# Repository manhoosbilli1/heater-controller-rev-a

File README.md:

# HEATER CONTROLLER REV_A

Battery-powered heater controller, 10 A switching, hierarchical schematic (ATtiny + OLED + dual-battery taps)

## At a Glance

- **Status**: Routed
- **Board size**: 47.24 x 45.82 mm
- **Layers**: 2
- **Components**: 75
- **Key ICs**:
  - U1: ATtiny3216-S
  - U2: DS18B20U
  - U3: TP4056
  - U4: INA234AxYBJ
  - U5,U6: TPS73001SF6
  - U7: TPS22997RYZR

## Schematic

Full PDF: [reports/schematic.pdf](reports/schematic.pdf)

## Component Roles

- **ATtiny** (in hierarchical sub-sheets) - main MCU; reads temperature and PWM-drives the heater MOSFET
- **CSD17578Q3A** (Q2) - 30 V, 100 A, 1.8 m-Ohm N-channel MOSFET; switches the heater load directly (low Rds(on) keeps conduction losses small at 10 A)
- **WS2812B** (D5) - status RGB LED
- **USB-C** charging input (power-only, 6P)
- **Dual battery taps** (TP1-TP4: BAT1+, BAT1-, BAT2+, BAT2-) for parallel/series battery configurations
- **Heater output taps** (TP5/TP6: HEATER_T1, HEATER_T2)
- Hierarchical schematic split across: Block Diagram, Project Architecture, Power-Sequencing, and Section A/B sub-sheets

## PCB

**Top copper**

**Bottom copper**

## Bill of Materials

| Refs | Value | Footprint | Qty | MPN | LCSC |
|------|-------|-----------|----:|-----|------|
| C1,C3-C7,C10,C12 | 100n | PCM_JLCPCB:C_0402 | 8 |  |  |
| C2 | 100u | Capacitor_SMD:C_0805_2012Metric | 1 |  | [C141660](https://www.lcsc.com/product-detail/_C141660.html) |
| C8,C9,C11,C13 | 2.2u | Capacitor_SMD:C_0805_2012Metric | 4 |  |  |
| D1,D6,D7 | Red | PCM_JLCPCB:D_0603 | 3 |  | [C2286](https://www.lcsc.com/product-detail/_C2286.html) |
| D2 | White | PCM_JLCPCB:D_0603 | 1 |  | [C2290](https://www.lcsc.com/product-detail/_C2290.html) |
| D3 | Yellow | PCM_JLCPCB:D_0603 | 1 |  | [C89811](https://www.lcsc.com/product-detail/_C89811.html) |
| D4 | Green | PCM_JLCPCB:D_0603 | 1 |  | [C122984](https://www.lcsc.com/product-detail/_C122984.html) |
| D5 | WS2812B | PCM_JLCPCB:LED_WS2812B_PLCC4_5.0x5.0mm_P3.2mm | 1 |  | [C22461793](https://www.lcsc.com/product-detail/_C22461793.html) |
| J5 | USB_C_Receptacle_PowerOnly_6P | Connector_USB:USB_C_Receptacle_GCT_USB4135-GF-A_6P_TopMnt_Horizontal | 1 |  |  |
| Q2 | CSD17578Q3A | mosfet_ti:PDFN3333-8_L3.1-W3.2-P0.65-LS3.4-BL | 1 |  |  |
| R1 | 4.7k | Resistor_SMD:R_0402_1005Metric | 1 |  |  |
| R2 | 1.2k | Resistor_SMD:R_0402_1005Metric | 1 |  |  |
| R3,R4 | 5.1k | Resistor_SMD:R_0402_1005Metric | 2 |  |  |
| R5,R6,R11,R12,R14,R15,R18,R19,R21,R24,R25 | 10k | Resistor_SMD:R_0402_1005Metric | 11 |  |  |
| R7-R10 | 330 | PCM_JLCPCB:R_0402 | 4 |  |  |
| R13 | 8m | Resistor_SMD:R_2512_6332Metric | 1 |  | [C2904240](https://www.lcsc.com/product-detail/_C2904240.html) |
| R16,R17 | 1k | PCM_JLCPCB:R_0402 | 2 |  |  |
| R20,R26 | 46k | Resistor_SMD:R_0402_1005Metric | 2 |  | [C3016791](https://www.lcsc.com/product-detail/_C3016791.html) |
| R23 | 330 | Resistor_SMD:R_0402_1005Metric | 1 |  |  |
| S1,S3 | Tactile Button, 160gf | PCM_JLCPCB:SW-SMD_4P-L5.1-W5.1-P3.70-LS6.5-TL-2 | 2 |  | [C318884](https://www.lcsc.com/product-detail/_C318884.html) |
| TP1 | BAT2+ | TestPoint:TestPoint_Pad_D4.0mm | 1 |  |  |
| TP2 | BAT2- | TestPoint:TestPoint_Pad_D4.0mm | 1 |  |  |
| TP3 | BAT1+ | TestPoint:TestPoint_Pad_D4.0mm | 1 |  |  |
| TP4 | BAT1- | TestPoint:TestPoint_Pad_D4.0mm | 1 |  |  |
| TP5 | HEATER_T2 | TestPoint:TestPoint_Pad_D4.0mm | 1 |  |  |
| TP6 | HEATER_T1 | TestPoint:TestPoint_Pad_D4.0mm | 1 |  |  |
| TP7,TP9,TP10 | IN+ | TestPoint:TestPoint_THTPad_2.0x2.0mm_Drill1.0mm | 3 |  |  |
| TP8 | IN- | TestPoint:TestPoint_THTPad_2.0x2.0mm_Drill1.0mm | 1 |  |  |
| TP11 | CT | TestPoint:TestPoint_THTPad_2.0x2.0mm_Drill1.0mm | 1 |  |  |
| TP12 | GATE | TestPoint:TestPoint_THTPad_2.0x2.0mm_Drill1.0mm | 1 |  |  |
| U1 | ATtiny3216-S | Package_SO:SOIC-20W_7.5x12.8mm_P1.27mm | 1 |  |  |
| U2 | DS18B20U | Package_SO:MSOP-8_3x3mm_P0.65mm | 1 |  |  |
| U3 | TP4056 | PCM_JLCPCB:ESOP-8_L4.9-W3.9-P1.27-LS6.0-BL-EP | 1 |  | [C16581](https://www.lcsc.com/product-detail/_C16581.html) |
| U4 | INA234AxYBJ | Package_BGA:Texas_DSBGA-8_0.705x1.468mm_Layout2x4_P0.4mm | 1 |  |  |
| U5,U6 | TPS73001SF6 | tps73001sf6:SOT-23-6_L2.9-W1.6-P0.95-LS2.8-BL | 2 |  |  |
| U7 | TPS22997RYZR | load_switch:UQFN-10_L2.0-W1.5-P0.50-TL | 1 |  |  |

_26 of 36 line items don't have an LCSC code in the schematic - search [LCSC](https://www.lcsc.com/) or [JLC parts search](https://jlcsearch.tscircuit.com/) by MPN or footprint when sourcing._

## Files

- `HEATER CONTROLLER REV_A.kicad_pro` - KiCad project
- `HEATER CONTROLLER REV_A.kicad_sch` - schematic source
- `HEATER CONTROLLER REV_A.kicad_pcb` - PCB layout source
- `reports/schematic.pdf` - full schematic (printable)
- `reports/bom.csv` - bill of materials
- `reports/pcb-top.svg`, `reports/pcb-bottom.svg` - copper artwork
- `reports/board-stats.json` - KiCad-generated board statistics

---

_Renders and metadata auto-generated by `Backup-KiCadProject.ps1` using KiCad 10.0._

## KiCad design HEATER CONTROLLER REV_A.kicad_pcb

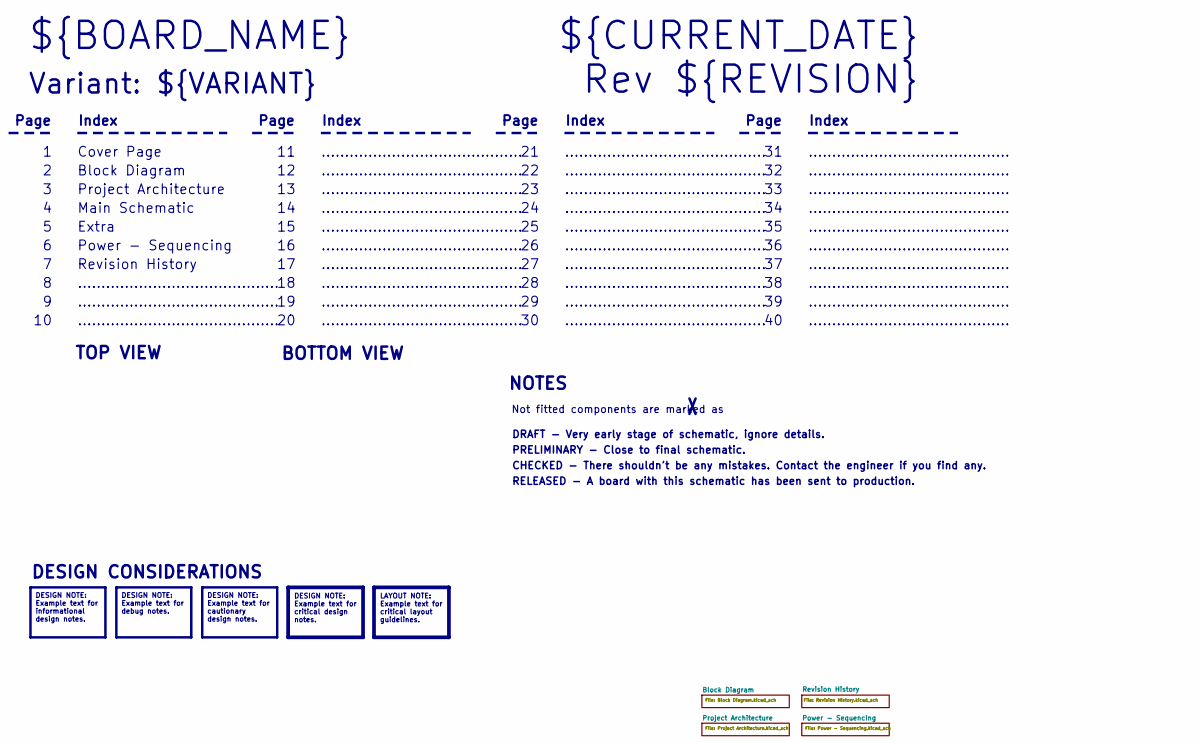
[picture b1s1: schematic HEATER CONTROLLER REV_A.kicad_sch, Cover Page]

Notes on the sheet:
BOTTOM VIEW
...........................................
RELEASED - A board with this schematic has been sent to production.
Page
TOP VIEW
Not fitted components are marked as
Index
PRELIMINARY - Close to final schematic.
Main Schematic
${CURRENT_DATE}
Variant: ${VARIANT}
Rev ${REVISION}
Extra
${BOARD_NAME}
DRAFT - Very early stage of schematic, ignore details.
Power - Sequencing
Block Diagram
Cover Page
NOTES
Project Architecture
CHECKED - There shouldn't be any mistakes. Contact the engineer if you find any.
DESIGN CONSIDERATIONS
Revision History
DESIGN NOTE: Example text for informational design notes.
LAYOUT NOTE: Example text for critical layout guidelines.
DESIGN NOTE: Example text for cautionary design notes.
DESIGN NOTE: Example text for debug notes.
DESIGN NOTE: Example text for critical design notes.

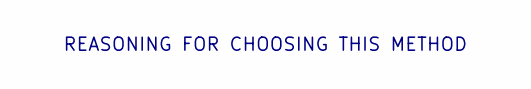
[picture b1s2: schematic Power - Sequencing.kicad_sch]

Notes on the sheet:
REASONING FOR CHOOSING THIS METHOD

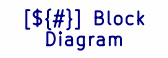
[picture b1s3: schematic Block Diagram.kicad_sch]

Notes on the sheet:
[${#}] ${TITLE}

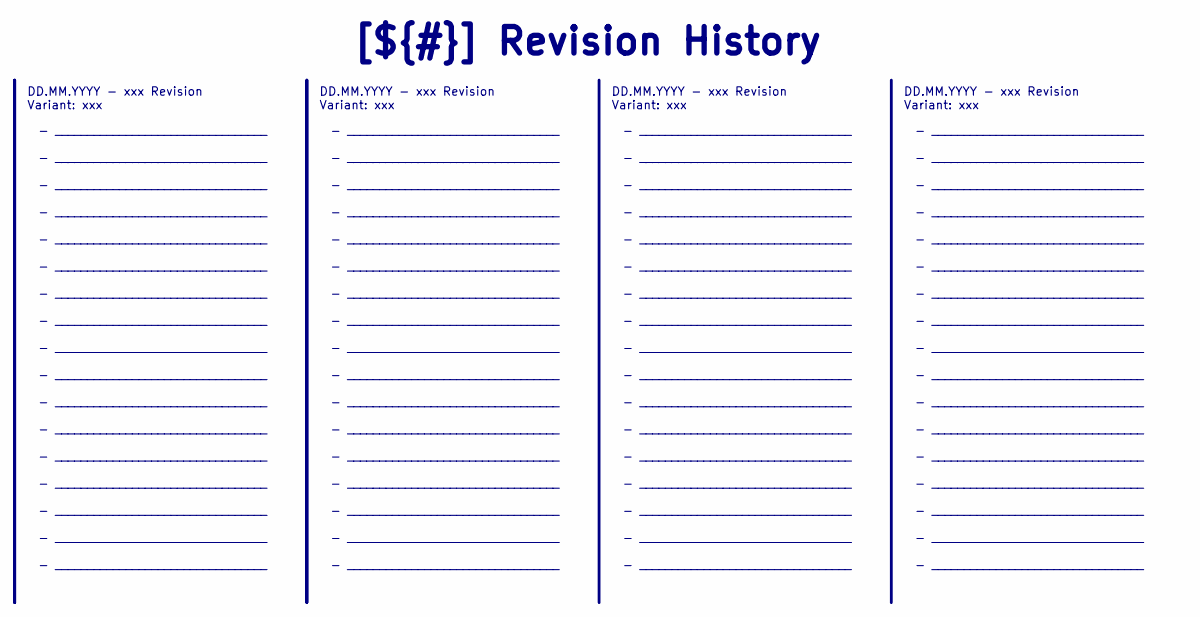
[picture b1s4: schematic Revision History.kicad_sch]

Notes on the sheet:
- _________________________________ - _________________________________ - _________________________________ - _________________________________ - _________________________________ - _________________________________ - _________________________________ - _________________________________ - _________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
DD.MM.YYYY - xxx Revision Variant: xxx
[${#}] ${TITLE}

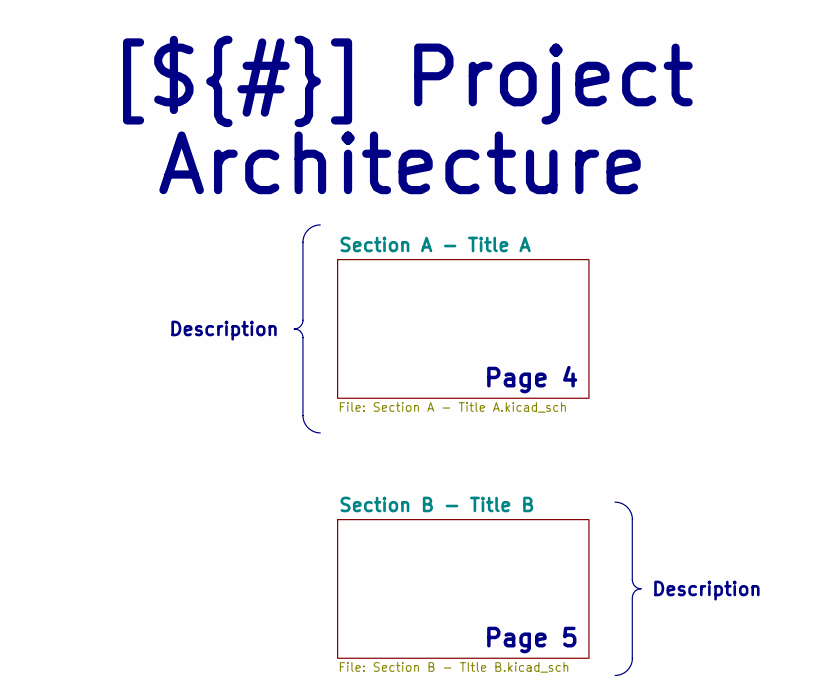
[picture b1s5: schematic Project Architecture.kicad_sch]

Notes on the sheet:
Page 4
Page 5
Description
[${#}] ${TITLE}

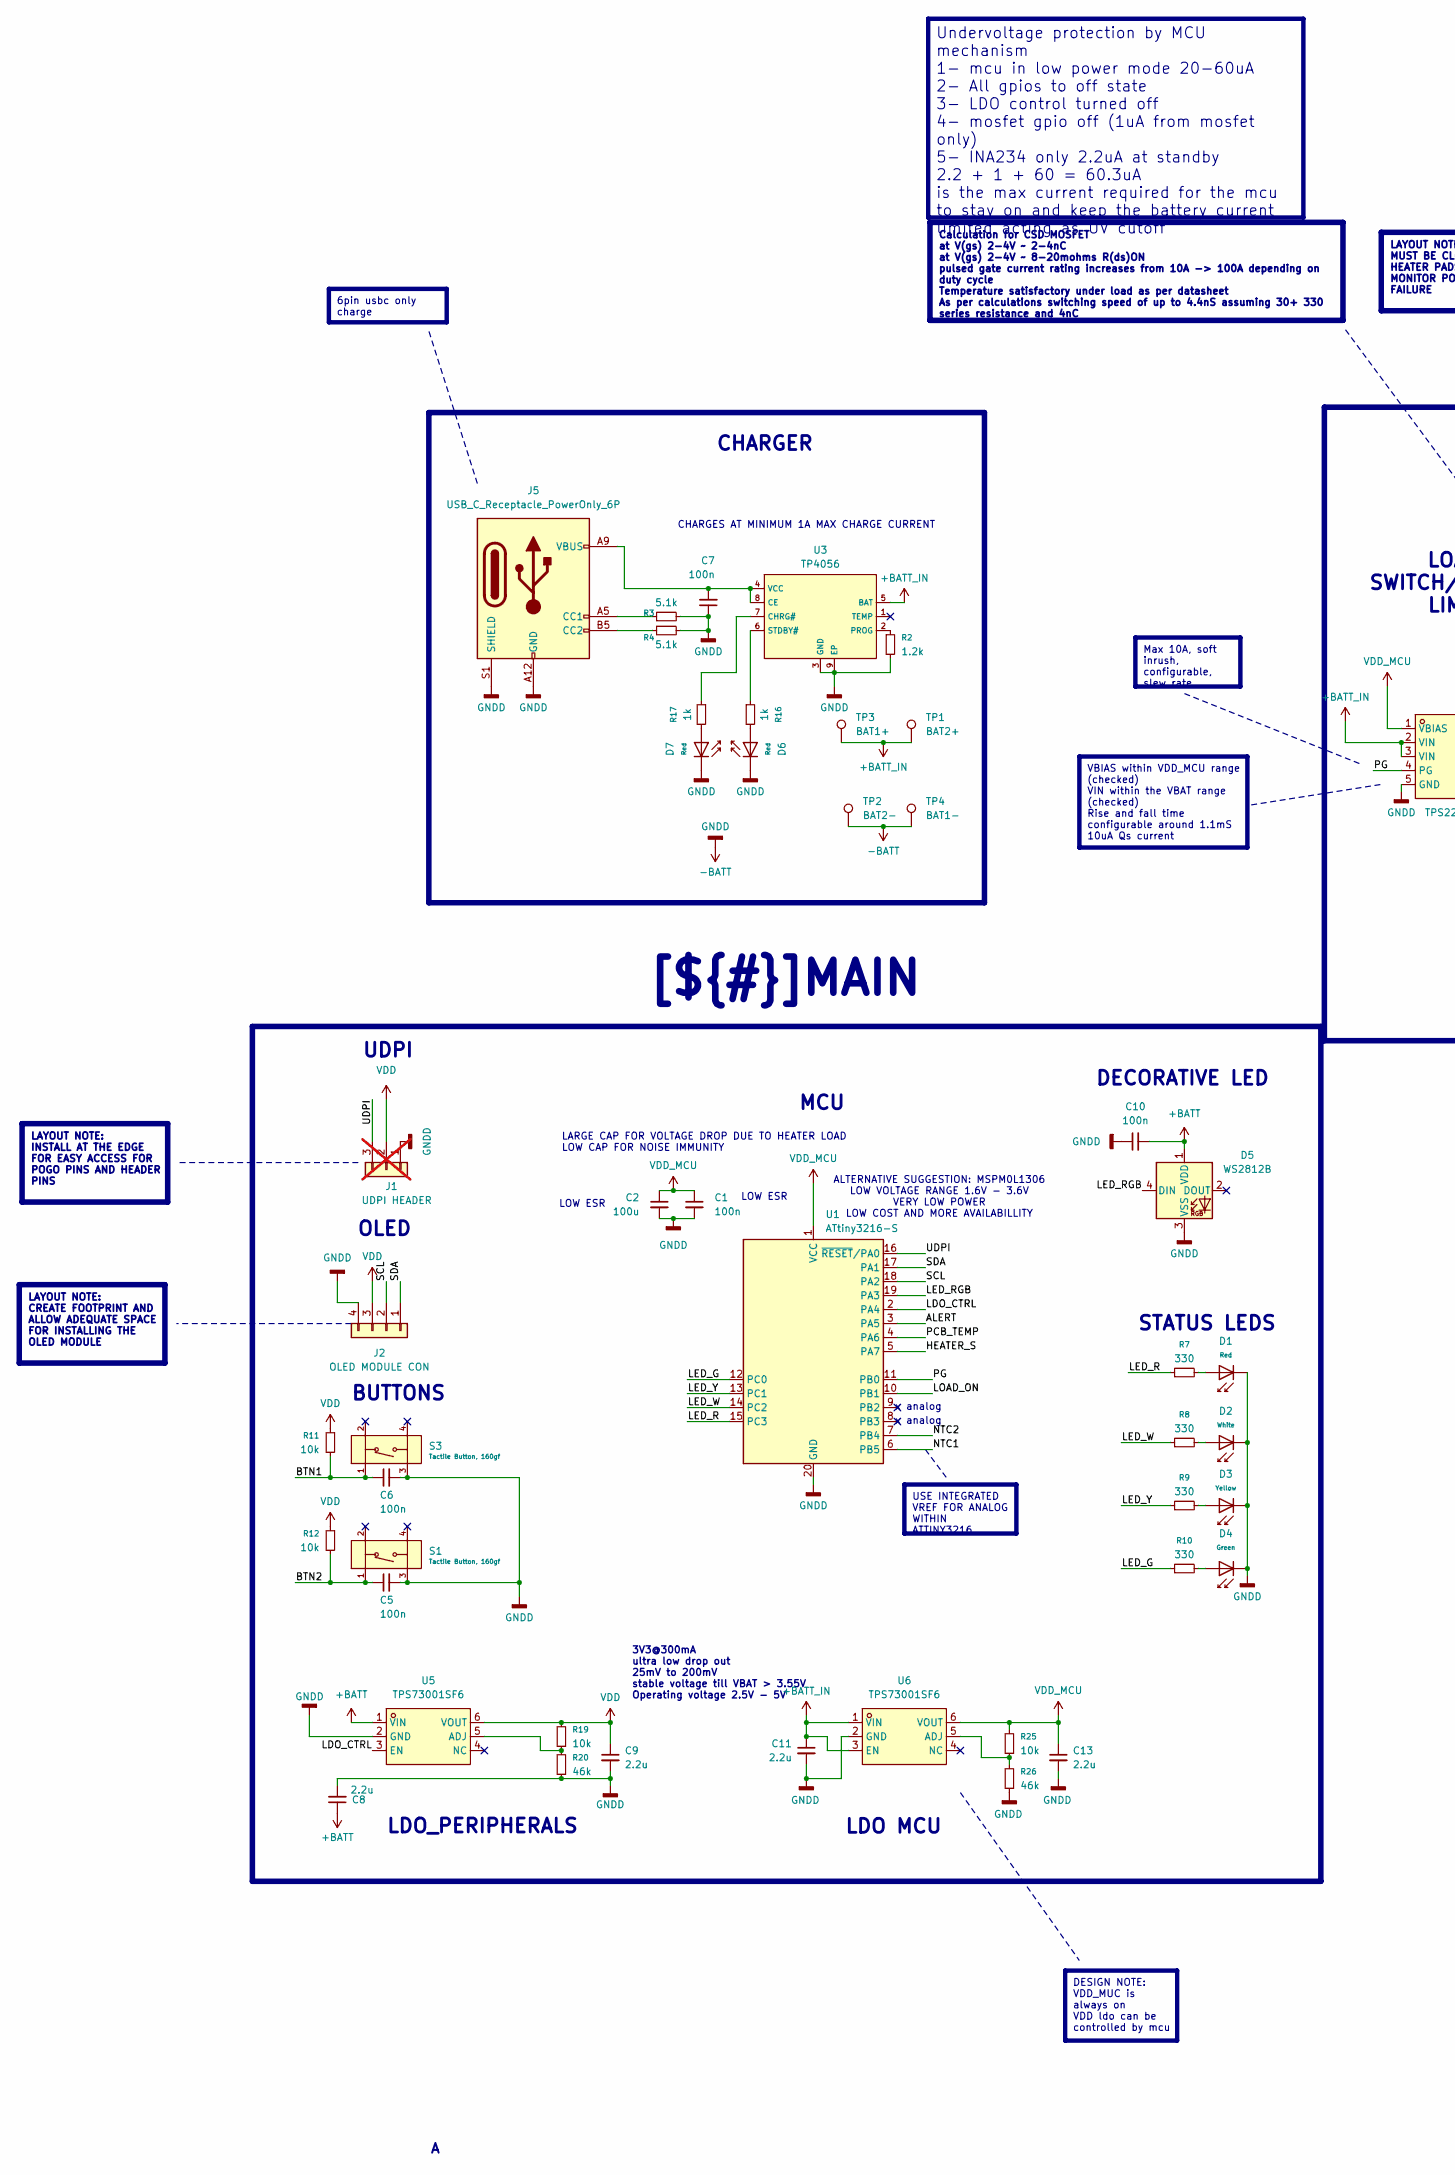
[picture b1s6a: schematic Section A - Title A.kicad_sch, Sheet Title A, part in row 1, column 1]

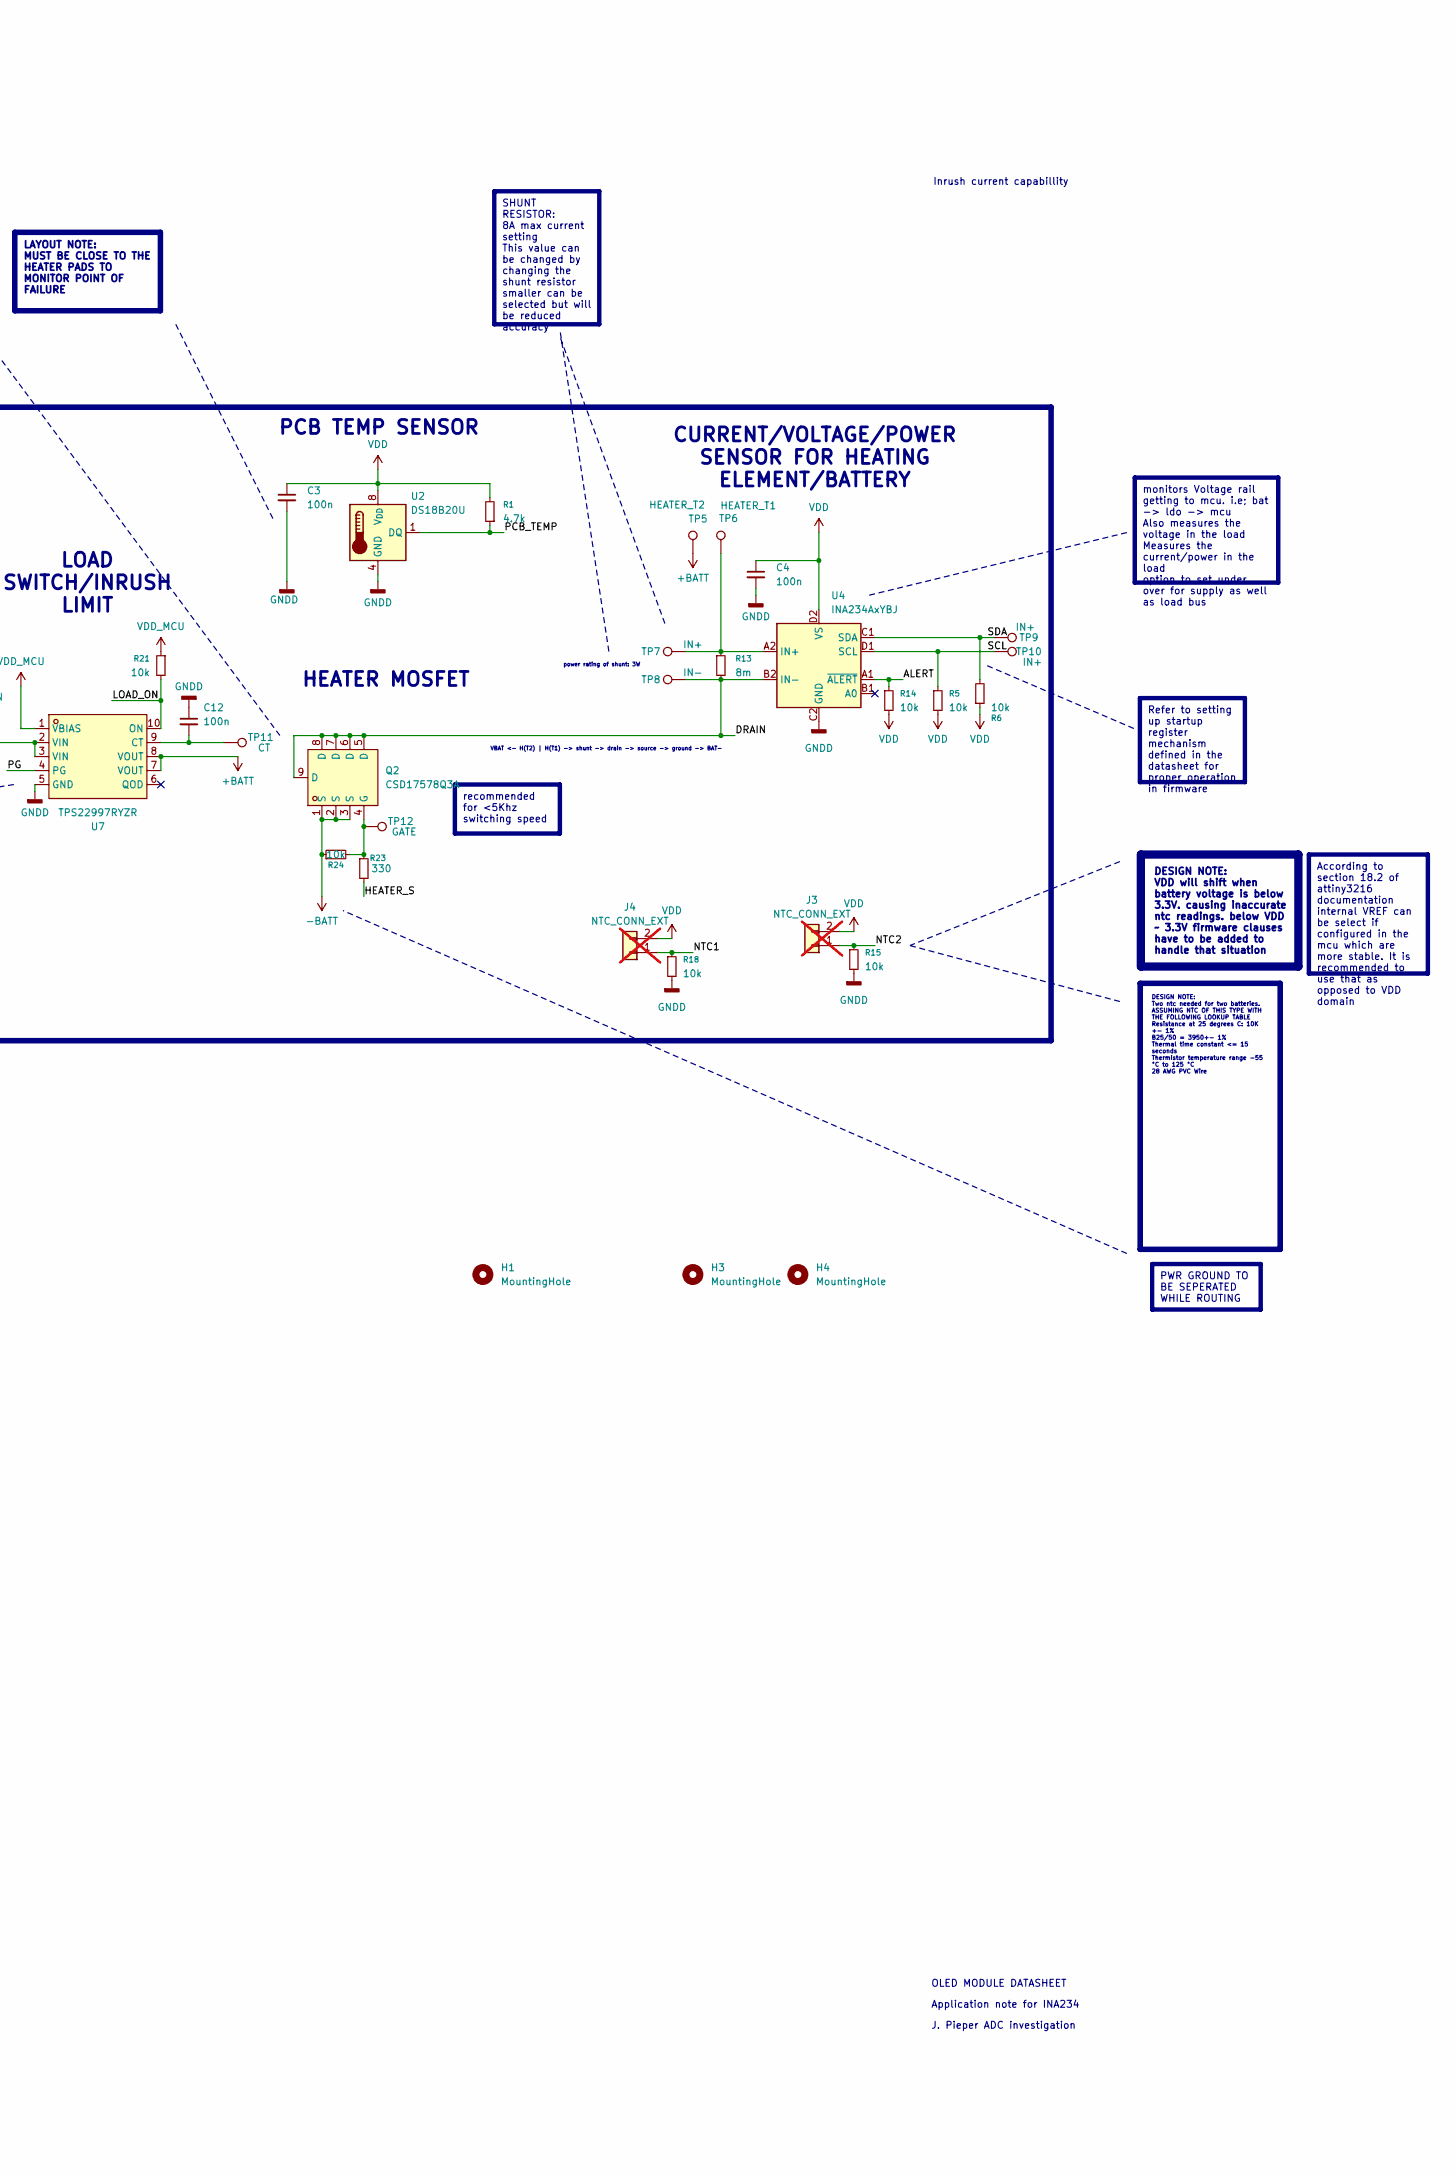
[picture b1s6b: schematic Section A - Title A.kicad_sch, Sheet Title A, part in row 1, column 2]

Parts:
C1, C3, C4, C5, C6, C7, C10, C12: 100n; C_0402
C2: 100u; C_0805_2012Metric; LCSC C141660
C8, C9, C11, C13: 2.2u; C_0805_2012Metric
D1, D6, D7: Red; D_0603; Part KT-0603R; LCSC C2286
D2: White; D_0603; Part KT-0603W; LCSC C2290
D3: Yellow; D_0603; Forward Voltage (VF) 1.6V~2.6V; Part NCD0603Y2; LCSC C89811
D4: Green; D_0603; Part KT-0805G; LCSC C122984
D5: WS2812B; LED_WS2812B_PLCC4_5.0x5.0mm_P3.2mm; LCSC C22461793
H1, H3, H4: MountingHole; MountingHole_3mm
J1: UDPI HEADER; PinSocket_1x03_P2.54mm_Vertical; not fitted
J2: OLED MODULE CON; PinHeader_1x04_P2.54mm_Vertical
J3, J4: NTC_CONN_EXT; PinSocket_1x02_P2.54mm_Vertical; not fitted
J5: USB_C_Receptacle_PowerOnly_6P; USB_C_Receptacle_GCT_USB4135-GF-A_6P_TopMnt_Horizontal
Q2: CSD17578Q3A; PDFN3333-8_L3.1-W3.2-P0.65-LS3.4-BL; LCSC Part C205986
R1: 4.7k; R_0402_1005Metric
R2: 1.2k; R_0402_1005Metric
R3, R4: 5.1k; R_0402_1005Metric
R5, R6, R11, R12, R14, R15, R18, R19, R21, R24, R25: 10k; R_0402_1005Metric
R7, R8, R9, R10: 330; R_0402
R13: 8m; R_2512_6332Metric; LCSC C2904240
R16, R17: 1k; R_0402
R20, R26: 46k; R_0402_1005Metric; LCSC C3016791
R23: 330; R_0402_1005Metric
S1, S3: Tactile Button, 160gf; SW-SMD_4P-L5.1-W5.1-P3.70-LS6.5-TL-2; Voltage Rating (Dc) 12V; Part TS-1187A-B-A-B; LCSC C318884
TP1: BAT2+; TestPoint_Pad_D4.0mm
TP2: BAT2-; TestPoint_Pad_D4.0mm
TP3: BAT1+; TestPoint_Pad_D4.0mm
TP4: BAT1-; TestPoint_Pad_D4.0mm
TP5: HEATER_T2; TestPoint_Pad_D4.0mm
TP6: HEATER_T1; TestPoint_Pad_D4.0mm
TP7, TP9, TP10: IN+; TestPoint_THTPad_2.0x2.0mm_Drill1.0mm
TP8: IN-; TestPoint_THTPad_2.0x2.0mm_Drill1.0mm
TP11: CT; TestPoint_THTPad_2.0x2.0mm_Drill1.0mm
TP12: GATE; TestPoint_THTPad_2.0x2.0mm_Drill1.0mm
U1: ATtiny3216-S; SOIC-20W_7.5x12.8mm_P1.27mm
U2: DS18B20U; MSOP-8_3x3mm_P0.65mm
U3: TP4056; ESOP-8_L4.9-W3.9-P1.27-LS6.0-BL-EP; Part TP4056-42-ESOP8; LCSC C16581
U4: INA234AxYBJ; Texas_DSBGA-8_0.705x1.468mm_Layout2x4_P0.4mm
U5, U6: TPS73001SF6; SOT-23-6_L2.9-W1.6-P0.95-LS2.8-BL; LCSC Part C2915259
U7: TPS22997RYZR; UQFN-10_L2.0-W1.5-P0.50-TL; LCSC Part C17286840

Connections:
+BATT: C8.1, C10.2, D5.1 (VDD), TP5.1, U5.1 (VIN), U7.7 (VOUT), U7.8 (VOUT)
+BATT_IN: C11.1, TP1.1, TP3.1, U3.5 (BAT), U6.1 (VIN), U6.3 (EN), U7.2 (VIN), U7.3 (VIN)
-BATT: C1.2, C2.2, C3.2, C4.2, C5.2, C6.2, C7.1, C8.2, C9.2, C10.1, C11.2, C12.1, C13.2, D1.1, D2.1, D3.1, D4.1, D5.3 (VSS), D6.1, D7.1, J1.1, J2.4, J5.A12 (GND), J5.B12 (GND), J5.S1 (SHIELD), Q2.1 (S), Q2.2 (S), Q2.3 (S), R2.2, R3.2, R4.2, R15.2, R18.2, R20.1, R24.1, R26.1, S1.3 (C), S3.3 (C), TP2.1, TP4.1, U1.20 (GND), U2.4 (GND), U3.3 (GND), U3.9 (EP), U4.C2 (GND), U5.2 (GND), U6.2 (GND), U7.5 (GND)
/Project Architecture/Section A - Title A/ALERT: R14.1, U1.3 (PA5), U4.A1 (~ALERT)
/Project Architecture/Section A - Title A/BTN1: C6.1, R11.2, S3.1 (A)
/Project Architecture/Section A - Title A/BTN2: C5.1, R12.2, S1.1 (A)
/Project Architecture/Section A - Title A/DRAIN: Q2.5 (D), Q2.6 (D), Q2.7 (D), Q2.8 (D), Q2.9 (D), R13.2, TP8.1, U4.B2 (IN-)
/Project Architecture/Section A - Title A/HEATER_S: R23.2, U1.5 (PA7)
/Project Architecture/Section A - Title A/LDO_CTRL: U1.2 (PA4), U5.3 (EN)
/Project Architecture/Section A - Title A/LED_G: R10.1, U1.12 (PC0)
/Project Architecture/Section A - Title A/LED_R: R7.1, U1.15 (PC3)
/Project Architecture/Section A - Title A/LED_RGB: D5.4 (DIN), U1.19 (PA3)
/Project Architecture/Section A - Title A/LED_W: R8.1, U1.14 (PC2)
/Project Architecture/Section A - Title A/LED_Y: R9.1, U1.13 (PC1)
/Project Architecture/Section A - Title A/LOAD_ON: R21.2, U1.10 (PB1), U7.10 (ON)
/Project Architecture/Section A - Title A/NTC1: J4.1, R18.1, U1.6 (PB5)
/Project Architecture/Section A - Title A/NTC2: J3.1, R15.1, U1.7 (PB4)
/Project Architecture/Section A - Title A/PCB_TEMP: R1.1, U1.4 (PA6), U2.1 (DQ)
/Project Architecture/Section A - Title A/PG: U1.11 (PB0), U7.4 (PG)
/Project Architecture/Section A - Title A/SCL: J2.2, R5.1, TP10.1, U1.18 (PA2), U4.D1 (SCL)
/Project Architecture/Section A - Title A/SDA: J2.1, R6.2, TP9.1, U1.17 (PA1), U4.C1 (SDA)
/Project Architecture/Section A - Title A/UDPI: J1.3, U1.16 (~RESET/PA0)
unnamed: D1.2, R7.2
unnamed: D2.2, R8.2
unnamed: D3.2, R9.2
unnamed: D4.2, R10.2
unnamed: D6.2, R16.2
unnamed: D7.2, R17.2
unnamed: J5.A5 (CC1), R3.1
unnamed: J5.B5 (CC2), R4.1
unnamed: Q2.4 (G), R23.1, R24.2, TP12.1
unnamed: C7.2, J5.A9 (VBUS), J5.B9 (VBUS), U3.4 (VCC), U3.8 (CE)
unnamed: R17.1, U3.7 (CHRG#)
unnamed: R2.1, U3.2 (PROG)
unnamed: R16.1, U3.6 (STDBY#)
unnamed: R13.1, TP6.1, TP7.1, U4.A2 (IN+)
unnamed: R19.1, R20.2, U5.5 (ADJ)
unnamed: R25.1, R26.2, U6.5 (ADJ)
unnamed: C12.2, TP11.1, U7.9 (CT)
VDD: C3.1, C4.1, C9.1, J1.2, J2.3, J3.2, J4.2, R1.2, R5.2, R6.1, R11.1, R12.1, R14.2, R19.2, U2.8 (V_{DD}), U4.D2 (VS), U5.6 (VOUT)
VDD_MCU: C1.1, C2.1, C13.1, R21.1, R25.2, U1.1 (VCC), U6.6 (VOUT), U7.1 (VBIAS)

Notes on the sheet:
3V3@300mA ultra low drop out 25mV to 200mV stable voltage till VBAT > 3.55V Operating voltage 2.5V - 5V
VBAT <- H(T2) | H(T1) -> shunt -> drain -> source -> ground -> BAT-
x analog
LOW ESR
ALTERNATIVE SUGGESTION: MSPM0L1306 LOW VOLTAGE RANGE 1.6V - 3.6V VERY LOW POWER LOW COST AND MORE AVAILABILLITY
Inrush current capabillity
CHARGES AT MINIMUM 1A MAX CHARGE CURRENT
J. Pieper ADC investigation
LARGE CAP FOR VOLTAGE DROP DUE TO HEATER LOAD LOW CAP FOR NOISE IMMUNITY
power rating of shunt: 3W
Application note for INA234
OLED MODULE DATASHEET
DESIGN NOTE: VDD will shift when battery voltage is below 3.3V. causing inaccurate ntc readings. below VDD ~ 3.3V firmware clauses have to be added to handle that situation
DECORATIVE LED
LDO_PERIPHERALS
UDPI
VBIAS within VDD_MCU range (checked) VIN within the VBAT range (checked) Rise and fall time configurable around 1.1mS 10uA Qs current
LDO MCU
CURRENT/VOLTAGE/POWER SENSOR FOR HEATING ELEMENT/BATTERY
BUTTONS
STATUS LEDS
LAYOUT NOTE: CREATE FOOTPRINT AND ALLOW ADEQUATE SPACE FOR INSTALLING THE OLED MODULE
6pin usbc only charge
Max 10A, soft inrush, configurable, slew rate
PWR GROUND TO BE SEPERATED WHILE ROUTING
Refer to setting up startup register mechanism defined in the datasheet for proper operation in firmware
DESIGN NOTE: VDD_MUC is always on VDD ldo can be controlled by mcu
Undervoltage protection by MCU mechanism 1- mcu in low power mode 20-60uA 2- All gpios to off state 3- LDO control turned off 4- mosfet gpio off (1uA from mosfet only) 5- INA234 only 2.2uA at standby 2.2 + 1 + 60 = 60.3uA is the max current required for the mcu to stay on and keep the battery curre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
HEATER MOSFET
LOAD SWITCH/INRUSH LIMIT
LAYOUT NOTE: INSTALL AT THE EDGE FOR EASY ACCESS FOR POGO PINS AND HEADER PINS
monitors Voltage rail getting to mcu. i.e; bat -> ldo -> mcu Also measures the voltage in the load Measures the current/power in the load option to set under, over for supply as well as load bus
SHUNT RESISTOR: 8A max current setting This value can be changed by changing the shunt resistor smaller can be selected but will be reduced accuracy
USE INTEGRATED VREF FOR ANALOG WITHIN ATTINY3216
CHARGER
PCB TEMP SENSOR
[${#}]MAIN
DESIGN NOTE: Two ntc needed for two batteries. ASSUMING NTC OF THIS TYPE WITH THE FOLLOWING LOOKUP TABLE Resistance at 25 degrees C: 10K +- 1% B25/50 = 3950+- 1% Thermal time constant <= 15 seconds Thermistor temperature range -55 °C to 125 °C 28 AWG PVC Wire
recommended for <5Khz switching speed
MCU

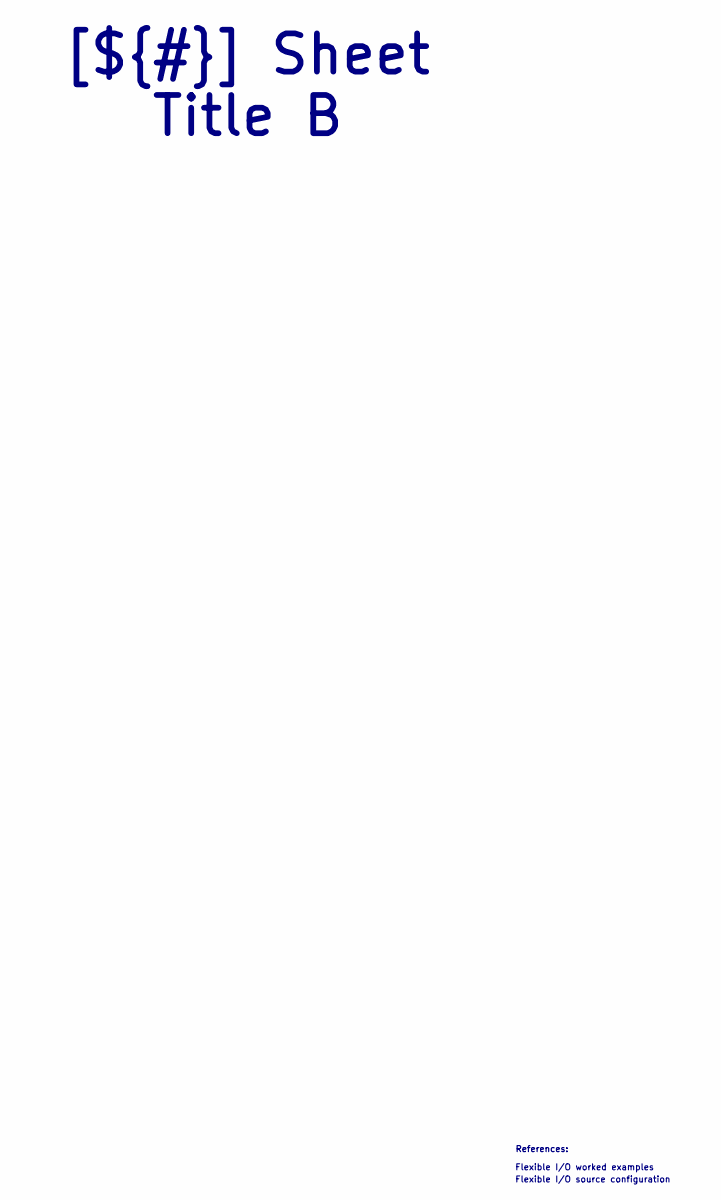
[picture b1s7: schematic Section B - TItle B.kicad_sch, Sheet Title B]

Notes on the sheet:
Flexible I/O worked examples
References:
Flexible I/O source configuration
[${#}] ${TITLE}

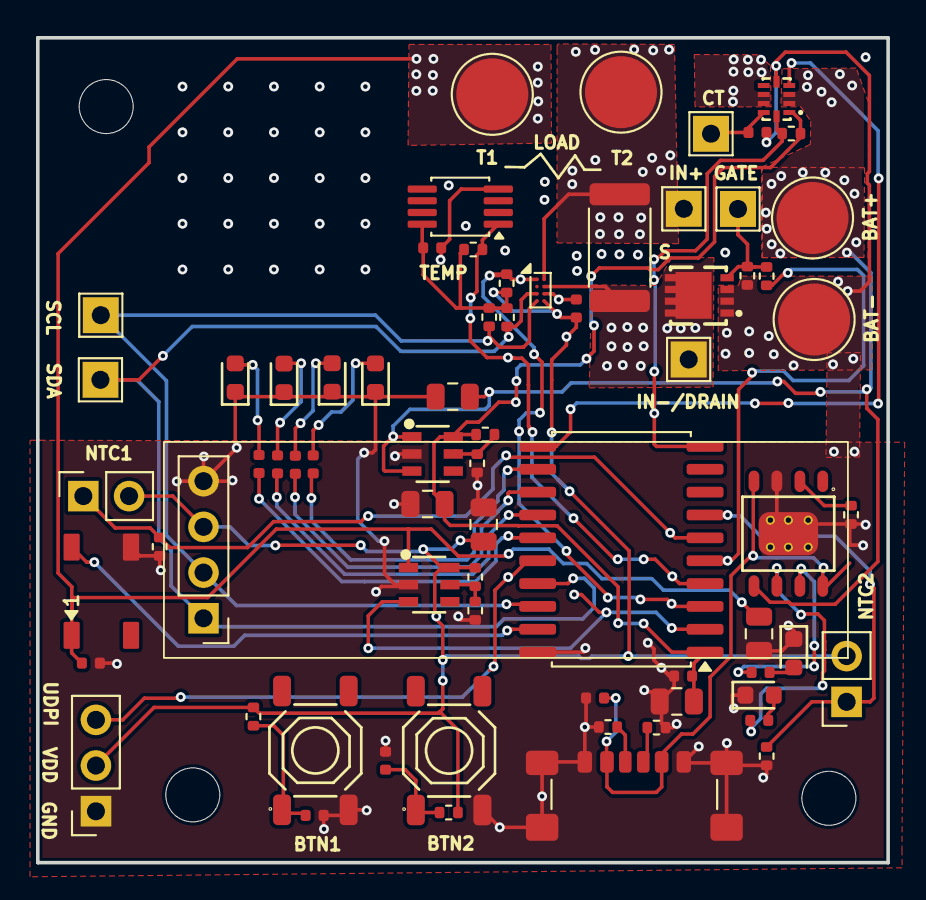
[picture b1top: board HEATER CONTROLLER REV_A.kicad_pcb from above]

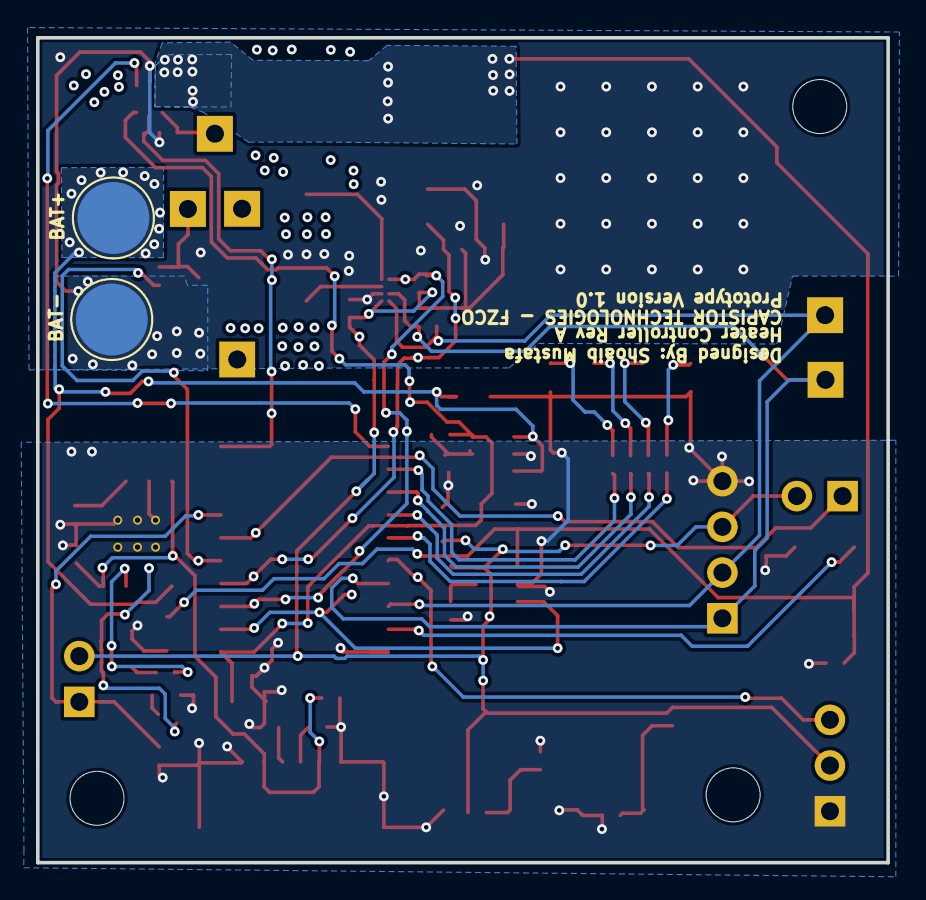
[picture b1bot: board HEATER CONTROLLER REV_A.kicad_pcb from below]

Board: 2 copper layers, 47.2 x 45.8 mm, 75 parts (2 on the bottom side), 41 nets.

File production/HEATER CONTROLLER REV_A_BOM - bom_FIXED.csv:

Designator,Footprint,Quantity,Value,LCSC Part #
"C1, C10, C12, C3, C4, C5, C6",C_0402,7,100n,
"C11, C13, C8, C9",C_0805,4,2.2u,
C2,C_0805,1,100u,
C7,C_0402,1,100n,
"D1, D6, D7",D_0603,3,Red,C2286
D2,D_0603,1,White,C2290
D3,D_0603,1,Yellow,C89811
D4,D_0603,1,Green,C122984
D5,LED_WS2812B_PLCC4_5.0x5.0mm_P3.2mm,1,WS2812B,C22461793
J5,USB_C_Receptacle_GCT_USB4135-GF-A_6P_TopMnt_Horizontal,1,USB_C_Receptacle_PowerOnly_6P,"
C2927028"
Q2,PDFN3333-8_L3.1-W3.2-P0.65-LS3.4-BL,1,CSD17578Q3A,C205986
R1,R_0402,1,4.7k,
"R10, R7, R8, R9",R_0402,4,330,
"R11, R12, R14, R15, R18, R19, R21, R24, R25, R5, R6",R_0402,11,10k,
R13,R_2512,1,8m,C2904240
"R16, R17",R_0402,2,1k,
R2,R_0402,1,1.2k,
"R20, R26",R_0402,2,46k,C3016791
R23,R_0402,1,330,
"R3, R4",R_0402,2,5.1k,
"S1, S3",SW-SMD_4P-L5.1-W5.1-P3.70-LS6.5-TL-2,2,"Tactile Button, 160gf",C318884
U1,SOIC-20W_7.5x12.8mm_P1.27mm,1,ATtiny3216-S,C609661
U2,MSOP-8_3x3mm_P0.65mm,1,DS18B20U,C4371066
U3,ESOP-8_L4.9-W3.9-P1.27-LS6.0-BL-EP,1,TP4056,C16581
U4,Texas_DSBGA-8_0.705x1.468mm_Layout2x4_P0.4mm,1,INA234AxYBJ,C4371066
"U5, U6",SOT-23-6_L2.9-W1.6-P0.95-LS2.8-BL,2,TPS73001SF6,C2915259
U7,UQFN-10_L2.0-W1.5-P0.50-TL,1,TPS22997RYZR,C17286840

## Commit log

2026-05-18 Initial backup: schematic, PCB, renders, BOM
2026-05-18 Enrich README: schematic PNG, component roles, BOM table
